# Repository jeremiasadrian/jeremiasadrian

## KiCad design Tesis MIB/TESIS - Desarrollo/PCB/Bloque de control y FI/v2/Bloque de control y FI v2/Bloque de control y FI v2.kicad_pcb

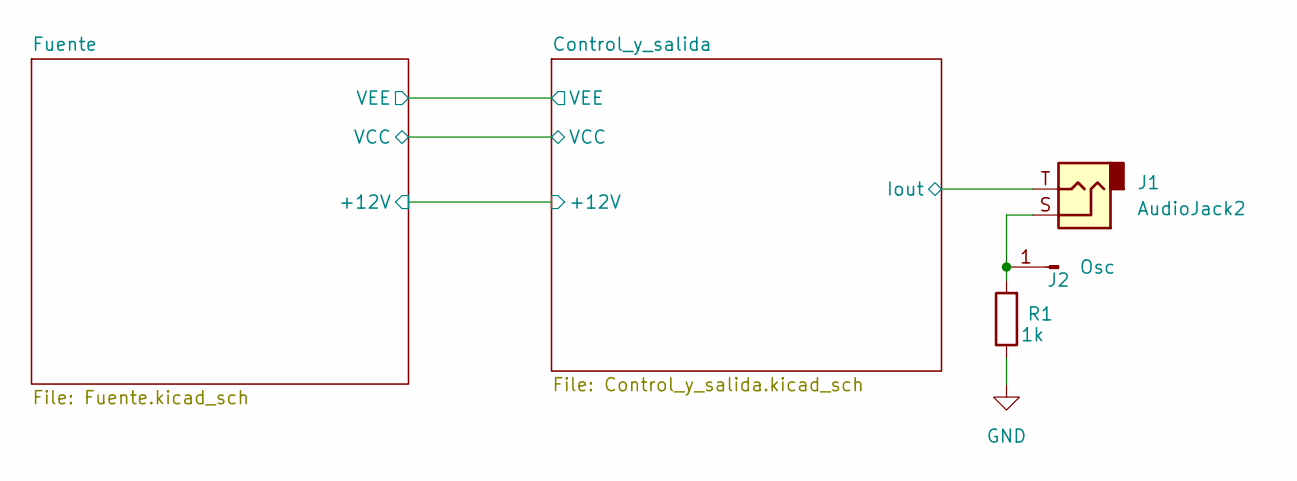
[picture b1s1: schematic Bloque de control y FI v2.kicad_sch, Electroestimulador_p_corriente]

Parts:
J1: AudioJack2; Jack_3.5mm_Ledino_KB3SPRS_Horizontal
J2: Osc; Pin_D0.9mm_L10.0mm_W2.4mm_FlatFork
R1: 1k; R_Axial_DIN0207_L6.3mm_D2.5mm_P10.16mm_Horizontal; Tolerancia 1%

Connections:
/Control_y_salida/Iout: J1.T; also elsewhere on the board
GND: R1.1; also elsewhere on the board
unnamed: J1.S, J2.1, R1.2

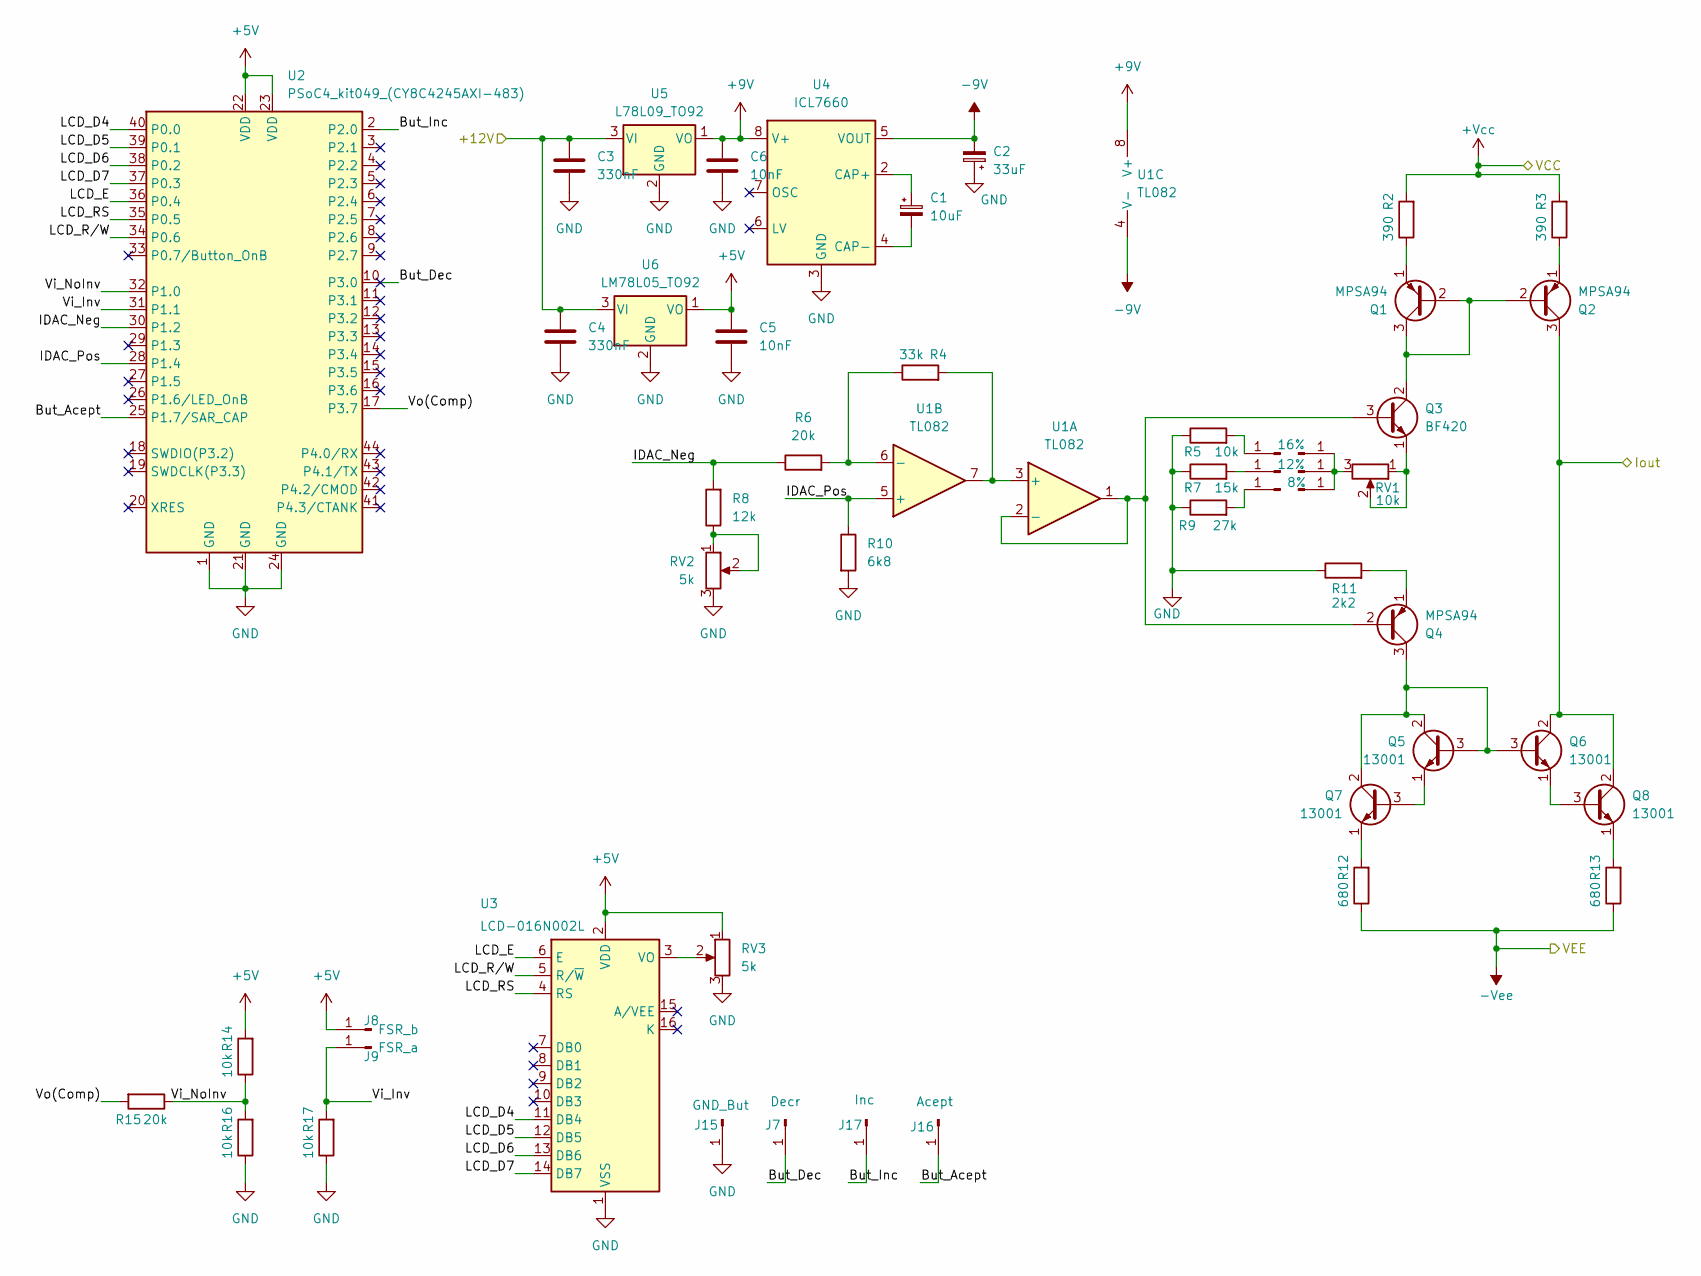
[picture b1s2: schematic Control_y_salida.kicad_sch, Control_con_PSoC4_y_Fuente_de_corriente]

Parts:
C1: 10uF; CP_Radial_D5.0mm_P2.50mm
C2: 33uF; CP_Radial_D5.0mm_P2.50mm
C3, C4: 330nF; C_Disc_D5.0mm_W2.5mm_P5.00mm
C5, C6: 10nF; C_Disc_D5.0mm_W2.5mm_P5.00mm
J5, J14: 16%; Pin_D0.9mm_L10.0mm_W2.4mm_FlatFork
J6, J12: 8%; Pin_D0.9mm_L10.0mm_W2.4mm_FlatFork
J7: Decr; Pin_D0.9mm_L10.0mm_W2.4mm_FlatFork
J8: FSR_b; Pin_D0.9mm_L10.0mm_W2.4mm_FlatFork
J9: FSR_a; Pin_D0.9mm_L10.0mm_W2.4mm_FlatFork
J11, J13: 12%; Pin_D0.9mm_L10.0mm_W2.4mm_FlatFork
J15: GND_But; Pin_D0.9mm_L10.0mm_W2.4mm_FlatFork
J16: Acept; Pin_D0.9mm_L10.0mm_W2.4mm_FlatFork
J17: Inc; Pin_D0.9mm_L10.0mm_W2.4mm_FlatFork
Q1, Q2, Q4: MPSA94; BF42X
Q3: BF420; BF42X
Q5, Q6, Q7, Q8: 13001; BF42X
R2, R3: 390; R_Axial_DIN0207_L6.3mm_D2.5mm_P10.16mm_Horizontal; Tolerancia 1%
R4: 33k; R_Axial_DIN0207_L6.3mm_D2.5mm_P10.16mm_Horizontal; Tolerancia 1%
R5, R14, R16, R17: 10k; R_Axial_DIN0207_L6.3mm_D2.5mm_P10.16mm_Horizontal; Tolerancia 1%
R6, R15: 20k; R_Axial_DIN0207_L6.3mm_D2.5mm_P10.16mm_Horizontal; Tolerancia 1%
R7: 15k; R_Axial_DIN0207_L6.3mm_D2.5mm_P10.16mm_Horizontal; Tolerancia 1%
R8: 12k; R_Axial_DIN0207_L6.3mm_D2.5mm_P10.16mm_Horizontal; Tolerancia 1%
R9: 27k; R_Axial_DIN0207_L6.3mm_D2.5mm_P10.16mm_Horizontal; Tolerancia 1%
R10: 6k8; R_Axial_DIN0207_L6.3mm_D2.5mm_P10.16mm_Horizontal; Tolerancia 1%
R11: 2k2; R_Axial_DIN0207_L6.3mm_D2.5mm_P10.16mm_Horizontal; Tolerancia 1%
R12, R13: 680; R_Axial_DIN0207_L6.3mm_D2.5mm_P10.16mm_Horizontal; Tolerancia 1%
RV1: 10k; Potentiometer_ACP_CA9-V10_Vertical
RV2, RV3: 5k; Potentiometer_Bourns_3296W_Vertical
U1: TL082; DIP-8_W7.62mm
U2: PSoC4_kit049_(CY8C4245AXI-483); PinSocket_2x22_P2.54mm_Vertical_3
U3: LCD-016N002L; LCD_pinsonly
U4: ICL7660; DIP-8_W7.62mm
U5: L78L09_TO92; TO-92_Inline_Wide
U6: LM78L05_TO92; TO-92_Inline_Wide

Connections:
+5V: C5.1, J8.1, R14.2, RV3.1, U2.22 (VDD), U2.23 (VDD), U3.2 (VDD), U6.1 (VO)
+9V: C6.1, U1.8 (V+), U4.8 (V+), U5.1 (VO)
-9V: C2.2, U1.4 (V-), U4.5 (VOUT)
/Control_y_salida/+12V: C3.1, C4.1, U5.3 (VI), U6.3 (VI); also elsewhere on the board
/Control_y_salida/But_Acept: J16.1, U2.25 (P1.7/SAR_CAP)
/Control_y_salida/But_Dec: J7.1, U2.10 (P3.0)
/Control_y_salida/But_Inc: J17.1, U2.2 (P2.0)
/Control_y_salida/IDAC_Neg: R6.1, R8.2, U2.30 (P1.2)
/Control_y_salida/IDAC_Pos: R10.1, U1.5 (+), U2.28 (P1.4)
/Control_y_salida/Iout: Q2.3 (C), Q6.2 (C), Q8.2 (C); also elsewhere on the board
/Control_y_salida/LCD_D4: U2.40 (P0.0), U3.11 (DB4)
/Control_y_salida/LCD_D5: U2.39 (P0.1), U3.12 (DB5)
/Control_y_salida/LCD_D6: U2.38 (P0.2), U3.13 (DB6)
/Control_y_salida/LCD_D7: U2.37 (P0.3), U3.14 (DB7)
/Control_y_salida/LCD_E: U2.36 (P0.4), U3.6 (E)
/Control_y_salida/LCD_RS: U2.35 (P0.5), U3.4 (RS)
/Control_y_salida/LCD_R/W: U2.34 (P0.6), U3.5 (R/~W)
/Control_y_salida/Vi_Inv: J9.1, R17.2, U2.31 (P1.1)
/Control_y_salida/Vi_NoInv: R14.1, R15.1, R16.2, U2.32 (P1.0)
/Control_y_salida/Vo(Comp): R15.2, U2.17 (P3.7)
GND: C2.1, C3.2, C4.2, C5.2, C6.2, J15.1, R5.1, R7.1, R9.1, R10.2, R11.1, R16.1, R17.1, RV2.3, RV3.3, U2.1 (GND), U2.21 (GND), U2.24 (GND), U3.1 (VSS), U4.3 (GND), U5.2 (GND), U6.2 (GND); also elsewhere on the board
unnamed: J5.1, R5.2
unnamed: J11.1, R7.2
unnamed: J12.1, R9.2
unnamed: J6.1, J13.1, J14.1, RV1.3
unnamed: Q1.2 (B), Q1.3 (C), Q2.2 (B), Q3.2 (C)
unnamed: Q1.1 (E), R2.1
unnamed: Q2.1 (E), R3.1
unnamed: Q3.3 (B), Q4.2 (B), U1.1, U1.2 (-)
unnamed: Q3.1 (E), RV1.1, RV1.2
unnamed: Q4.3 (C), Q5.2 (C), Q5.3 (B), Q6.3 (B), Q7.2 (C)
unnamed: Q4.1 (E), R11.2
unnamed: Q5.1 (E), Q7.3 (B)
unnamed: Q6.1 (E), Q8.3 (B)
unnamed: Q7.1 (E), R12.2
unnamed: Q8.1 (E), R13.2
unnamed: R8.1, RV2.1, RV2.2
unnamed: R4.2, U1.3 (+), U1.7
unnamed: R4.1, R6.2, U1.6 (-)
unnamed: RV3.2, U3.3 (VO)
unnamed: C1.1, U4.2 (CAP+)
unnamed: C1.2, U4.4 (CAP-)
VCC: R2.2, R3.2; also elsewhere on the board
VEE: R12.1, R13.1; also elsewhere on the board

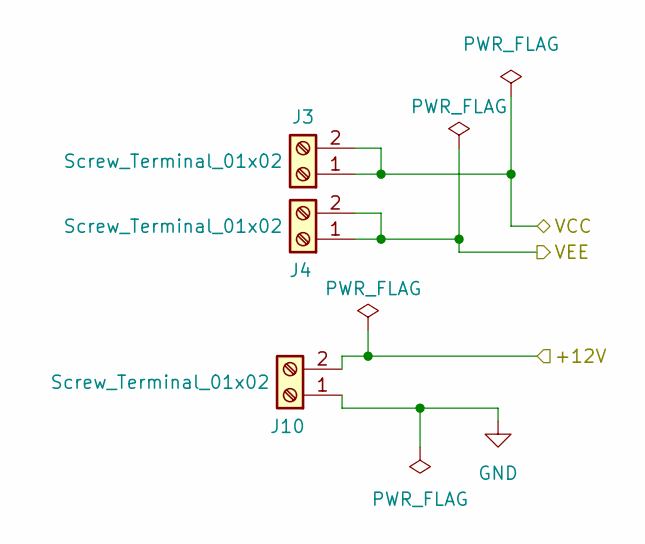
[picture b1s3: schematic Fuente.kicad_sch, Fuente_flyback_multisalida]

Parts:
J3, J4, J10: Screw_Terminal_01x02; TerminalBlock_bornier-2_P5.08mm

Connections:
/Control_y_salida/+12V: J10.2; also elsewhere on the board
GND: J10.1; also elsewhere on the board
VCC: J3.1, J3.2; also elsewhere on the board
VEE: J4.1, J4.2; also elsewhere on the board

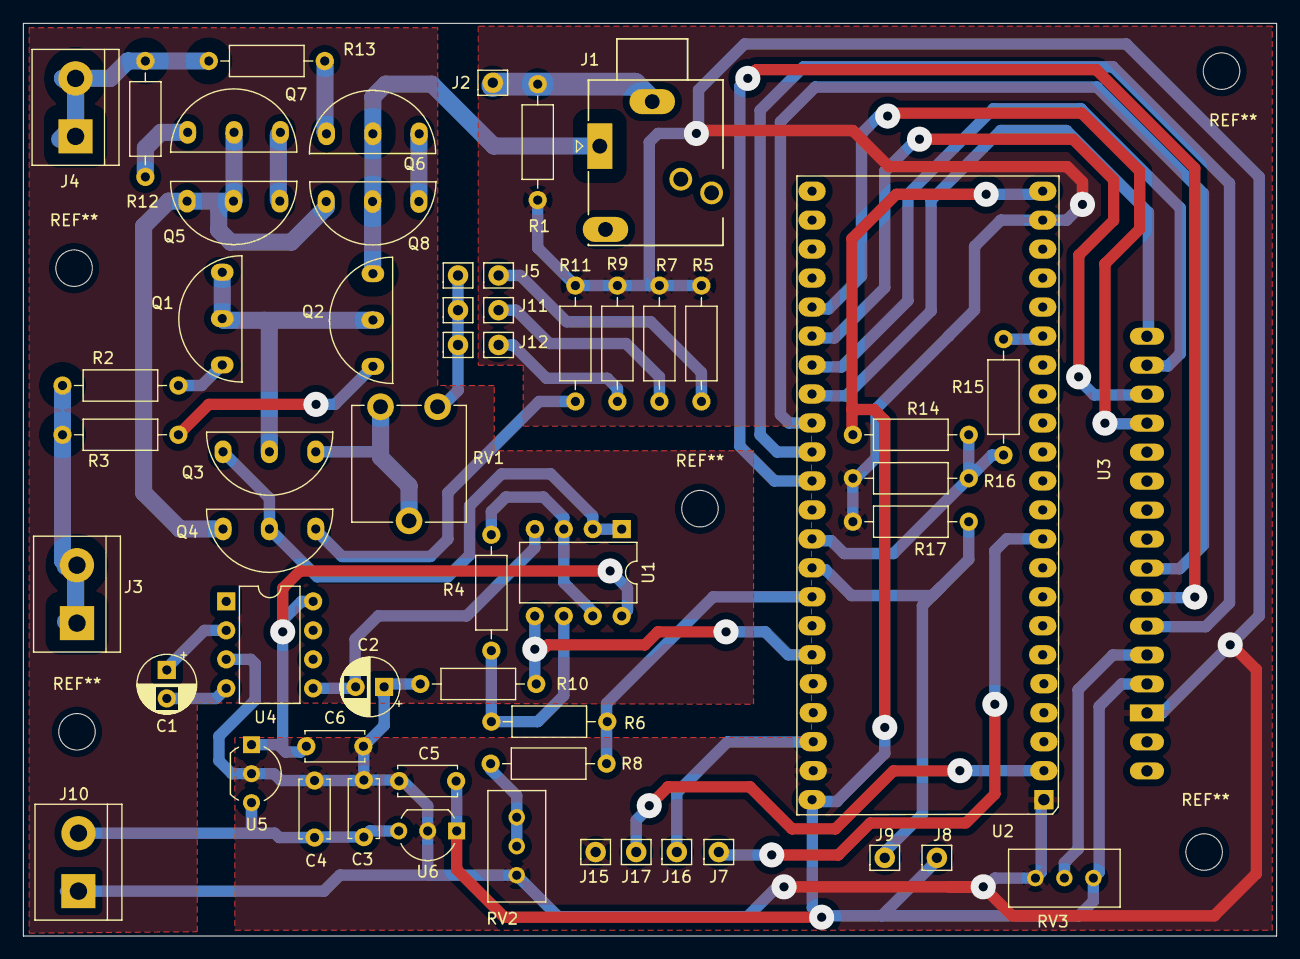
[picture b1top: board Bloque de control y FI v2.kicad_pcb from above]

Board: 2 copper layers, 109.9 x 80.0 mm, 57 parts (0 on the bottom side), 45 nets.

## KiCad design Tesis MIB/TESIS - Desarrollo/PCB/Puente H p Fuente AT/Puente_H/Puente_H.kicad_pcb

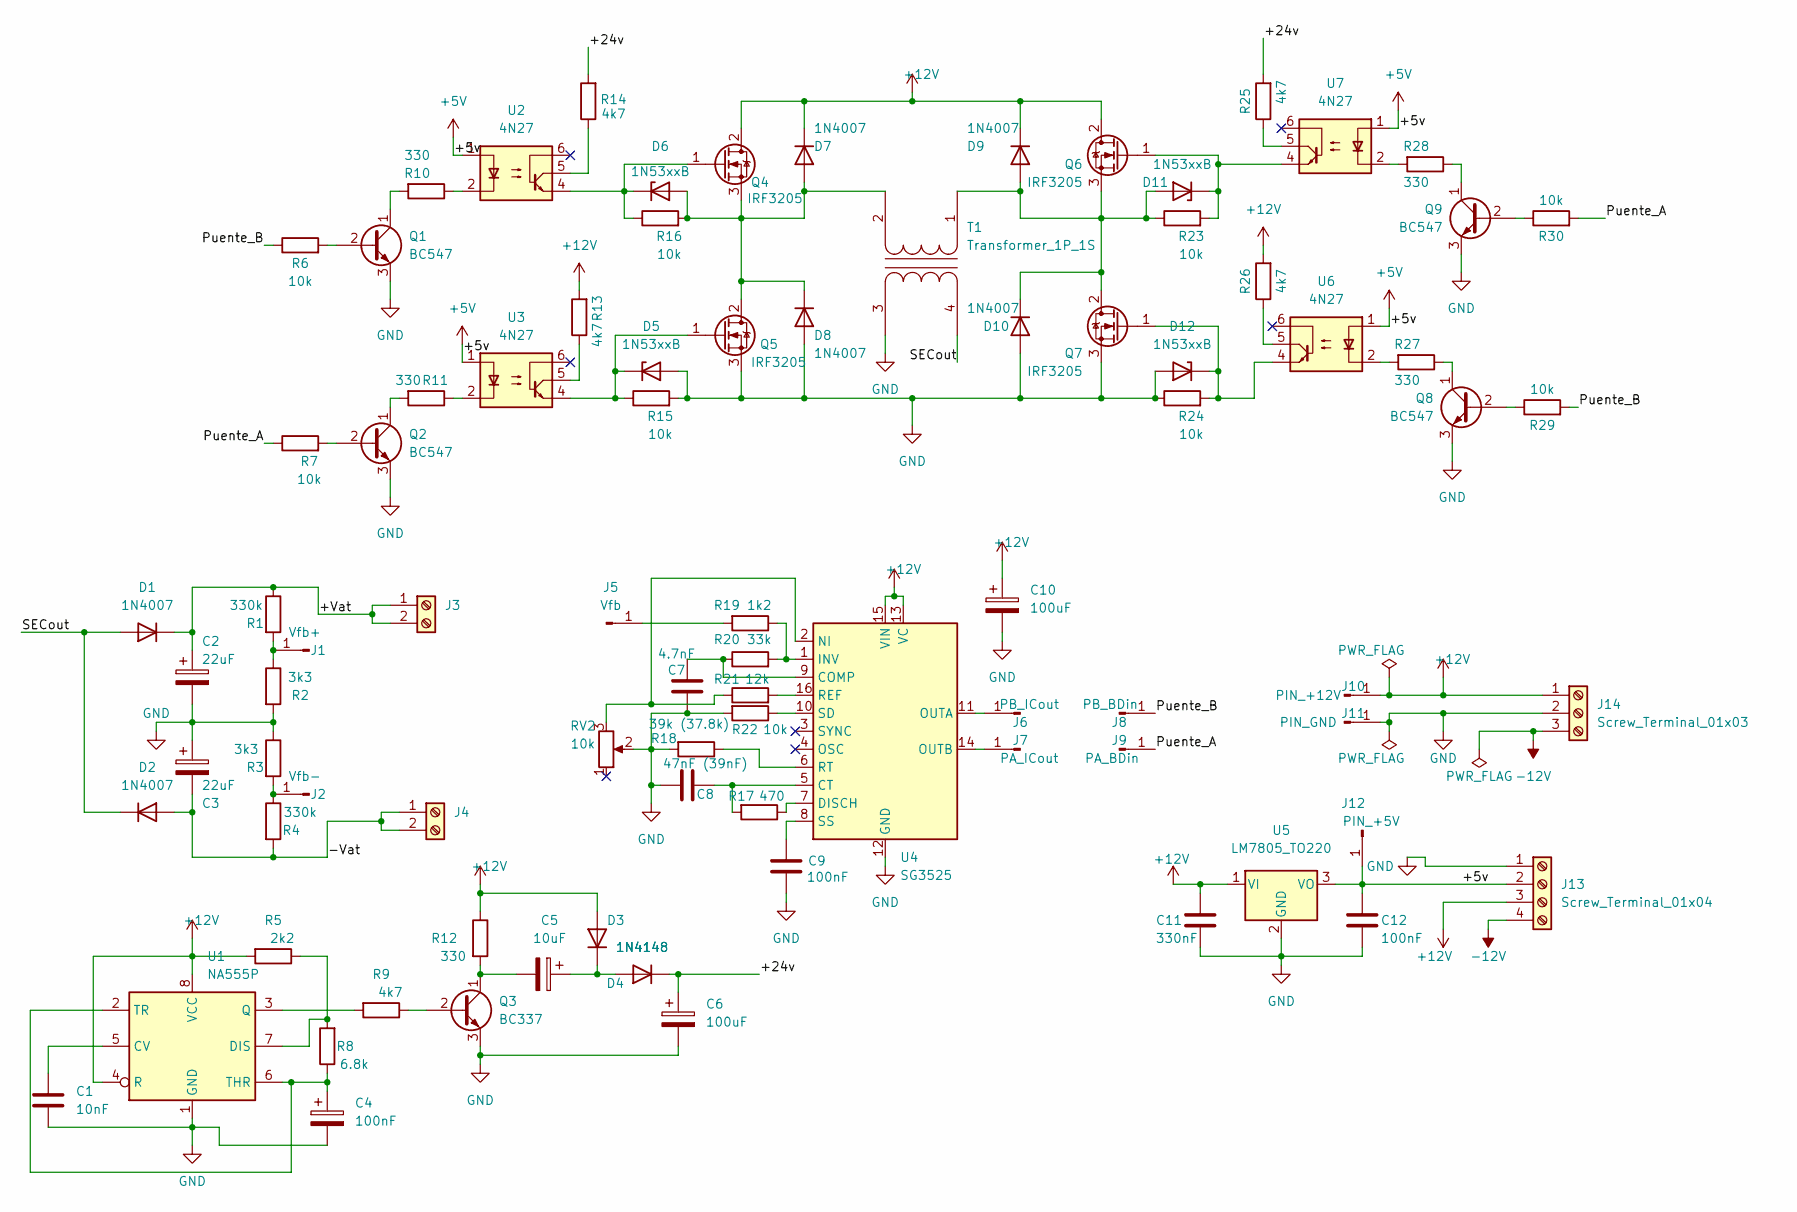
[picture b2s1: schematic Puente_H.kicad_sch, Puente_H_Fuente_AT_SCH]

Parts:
C1: 10nF; C_Disc_D5.0mm_W2.5mm_P2.50mm
C2, C3: 22uF; CP_Radial_D16.0mm_P7.50mm
C4, C9, C12: 100nF; C_Disc_D5.0mm_W2.5mm_P2.50mm
C5: 10uF; CP_Radial_D6.3mm_P2.50mm
C6, C10: 100uF; CP_Radial_D6.3mm_P2.50mm
C7: 4.7nF; C_Disc_D5.0mm_W2.5mm_P2.50mm
C8: 47nF (39nF); C_Disc_D5.0mm_W2.5mm_P2.50mm
C11: 330nF; C_Disc_D5.0mm_W2.5mm_P2.50mm
D1, D2, D7, D8, D9, D10: 1N4007; D_DO-41_SOD81_P10.16mm_Horizontal
D3, D4: 1N4148; D_DO-35_SOD27_P7.62mm_Horizontal
D5, D6, D11, D12: 1N53xxB; D_DO-35_SOD27_P7.62mm_Horizontal
J1: Vfb+; Pin_D0.7mm_L6.5mm_W1.8mm_FlatFork
J2: Vfb-; Pin_D0.7mm_L6.5mm_W1.8mm_FlatFork
J3, J4: Screw_Terminal_01x02; TerminalBlock_bornier-2_P5.08mm
J5: Vfb; Pin_D0.7mm_L6.5mm_W1.8mm_FlatFork
J6: PB_ICout; Pin_D0.7mm_L6.5mm_W1.8mm_FlatFork
J7: PA_ICout; Pin_D0.7mm_L6.5mm_W1.8mm_FlatFork
J8: PB_BDin; Pin_D0.7mm_L6.5mm_W1.8mm_FlatFork
J9: PA_BDin; Pin_D0.7mm_L6.5mm_W1.8mm_FlatFork
J10: PIN_+12V; Pin_D0.7mm_L6.5mm_W1.8mm_FlatFork
J11: PIN_GND; Pin_D0.7mm_L6.5mm_W1.8mm_FlatFork
J12: PIN_+5V; Pin_D0.7mm_L6.5mm_W1.8mm_FlatFork
J13: Screw_Terminal_01x04; TerminalBlock_bornier-4_P5.08mm
J14: Screw_Terminal_01x03; TerminalBlock_bornier-3_P5.08mm
Q1, Q2, Q8, Q9: BC547; TO-92_Inline_Wide
Q3: BC337; TO-92_Inline_Wide
Q4, Q5, Q6, Q7: IRF3205; TO-220-3_Vertical
R1, R4: 330k; R_Axial_DIN0207_L6.3mm_D2.5mm_P7.62mm_Horizontal
R2, R3: 3k3; R_Axial_DIN0207_L6.3mm_D2.5mm_P7.62mm_Horizontal
R5: 2k2; R_Axial_DIN0207_L6.3mm_D2.5mm_P7.62mm_Horizontal
R6, R7, R15, R16, R22, R23, R24, R29, R30: 10k; R_Axial_DIN0207_L6.3mm_D2.5mm_P7.62mm_Horizontal
R8: 6.8k; R_Axial_DIN0207_L6.3mm_D2.5mm_P7.62mm_Horizontal
R9, R13, R14, R25, R26: 4k7; R_Axial_DIN0207_L6.3mm_D2.5mm_P7.62mm_Horizontal
R10, R11, R12, R27, R28: 330; R_Axial_DIN0207_L6.3mm_D2.5mm_P7.62mm_Horizontal
R17: 470; R_Axial_DIN0207_L6.3mm_D2.5mm_P7.62mm_Horizontal
R18: 39k (37.8k); R_Axial_DIN0207_L6.3mm_D2.5mm_P7.62mm_Horizontal
R19: 1k2; R_Axial_DIN0207_L6.3mm_D2.5mm_P7.62mm_Horizontal
R20: 33k; R_Axial_DIN0207_L6.3mm_D2.5mm_P7.62mm_Horizontal
R21: 12k; R_Axial_DIN0207_L6.3mm_D2.5mm_P7.62mm_Horizontal
RV2: 10k; Potentiometer_Bourns_3296W_Vertical
T1: Transformer_1P_1S; Transformer_1S_2P
U1: NA555P; DIP-8_W7.62mm
U2, U3, U6, U7: 4N27; DIP-6_W7.62mm
U4: SG3525; DIP-16_W7.62mm_LongPads
U5: LM7805_TO220; TO-220-3_Vertical

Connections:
+5V: C12.1, J12.1, J13.2, U2.1, U3.1, U5.3 (VO), U6.1, U7.1
+12V: C10.1, C11.1, D3.2 (A), D7.1 (K), D9.1 (K), J10.1, J13.3, J14.1, Q4.2 (D), Q6.2 (D), R5.2, R12.1, R13.2, R26.2, U1.4 (R), U1.8 (VCC), U4.13 (VC), U4.15 (VIN), U5.1 (VI)
-12V: J13.4, J14.3
/+24v: C6.1, D4.1 (K), R14.2, R25.2
/+Vat: C2.1, D1.1 (K), J3.1, J3.2, R1.1
/-Vat: C3.2, D2.2 (A), J4.1, J4.2, R4.2
/Puente_A: J9.1, R7.1, R30.2
/Puente_B: J8.1, R6.1, R29.2
/SECout: D1.2 (A), D2.1 (K), T1.4 (SB)
GND: C1.2, C2.2, C3.1, C4.2, C6.2, C7.2, C8.1, C9.1, C10.2, C11.2, C12.2, D5.2 (A), D8.2 (A), D10.2 (A), D12.2 (A), J11.1, J13.1, J14.2, Q1.3 (E), Q2.3 (E), Q3.3 (E), Q5.3 (S), Q7.3 (S), Q8.3 (E), Q9.3 (E), R2.2, R3.1, R15.2, R18.2, R22.2, R24.1, RV2.2, T1.3 (SA), U1.1 (GND), U4.12 (GND), U5.2 (GND)
unnamed: C5.1, D3.1 (K), D4.2 (A)
unnamed: D5.1 (K), Q5.1 (G), R15.1, U3.4
unnamed: D6.2 (A), D7.2 (A), D8.1 (K), Q4.3 (S), Q5.2 (D), R16.2, T1.2 (AB)
unnamed: D6.1 (K), Q4.1 (G), R16.1, U2.4
unnamed: D9.2 (A), D10.1 (K), D11.2 (A), Q6.3 (S), Q7.2 (D), R23.1, T1.1 (AA)
unnamed: D11.1 (K), Q6.1 (G), R23.2, U7.4
unnamed: D12.1 (K), Q7.1 (G), R24.2, U6.4
unnamed: J1.1, R1.2, R2.1
unnamed: J2.1, R3.2, R4.1
unnamed: J5.1, R19.2
unnamed: J6.1, U4.11 (OUTA)
unnamed: J7.1, U4.14 (OUTB)
unnamed: Q1.2 (B), R6.2
unnamed: Q1.1 (C), R10.2
unnamed: Q2.2 (B), R7.2
unnamed: Q2.1 (C), R11.2
unnamed: Q3.2 (B), R9.1
unnamed: C5.2, Q3.1 (C), R12.2
unnamed: Q8.2 (B), R29.1
unnamed: Q8.1 (C), R27.1
unnamed: Q9.2 (B), R30.1
unnamed: Q9.1 (C), R28.1
unnamed: R10.1, U2.2
unnamed: R11.1, U3.2
unnamed: R13.1, U3.5
unnamed: R14.1, U2.5
unnamed: R25.1, U7.5
unnamed: R26.1, U6.5
unnamed: R27.2, U6.2
unnamed: R28.2, U7.2
unnamed: C1.1, U1.5 (CV)
unnamed: R5.1, R8.2, U1.7 (DIS)
unnamed: R9.2, U1.3 (Q)
unnamed: C4.1, R8.1, U1.2 (TR), U1.6 (THR)
unnamed: C7.1, R20.1, U4.9 (COMP)
unnamed: C8.2, R17.2, U4.5 (CT)
unnamed: R17.1, U4.7 (DISCH)
unnamed: R19.1, R20.2, U4.1 (INV)
unnamed: R21.1, RV2.3, U4.2 (NI)
unnamed: R21.2, U4.16 (REF)
unnamed: R18.1, U4.6 (RT)
unnamed: R22.1, U4.10 (SD)
unnamed: C9.2, U4.8 (SS)

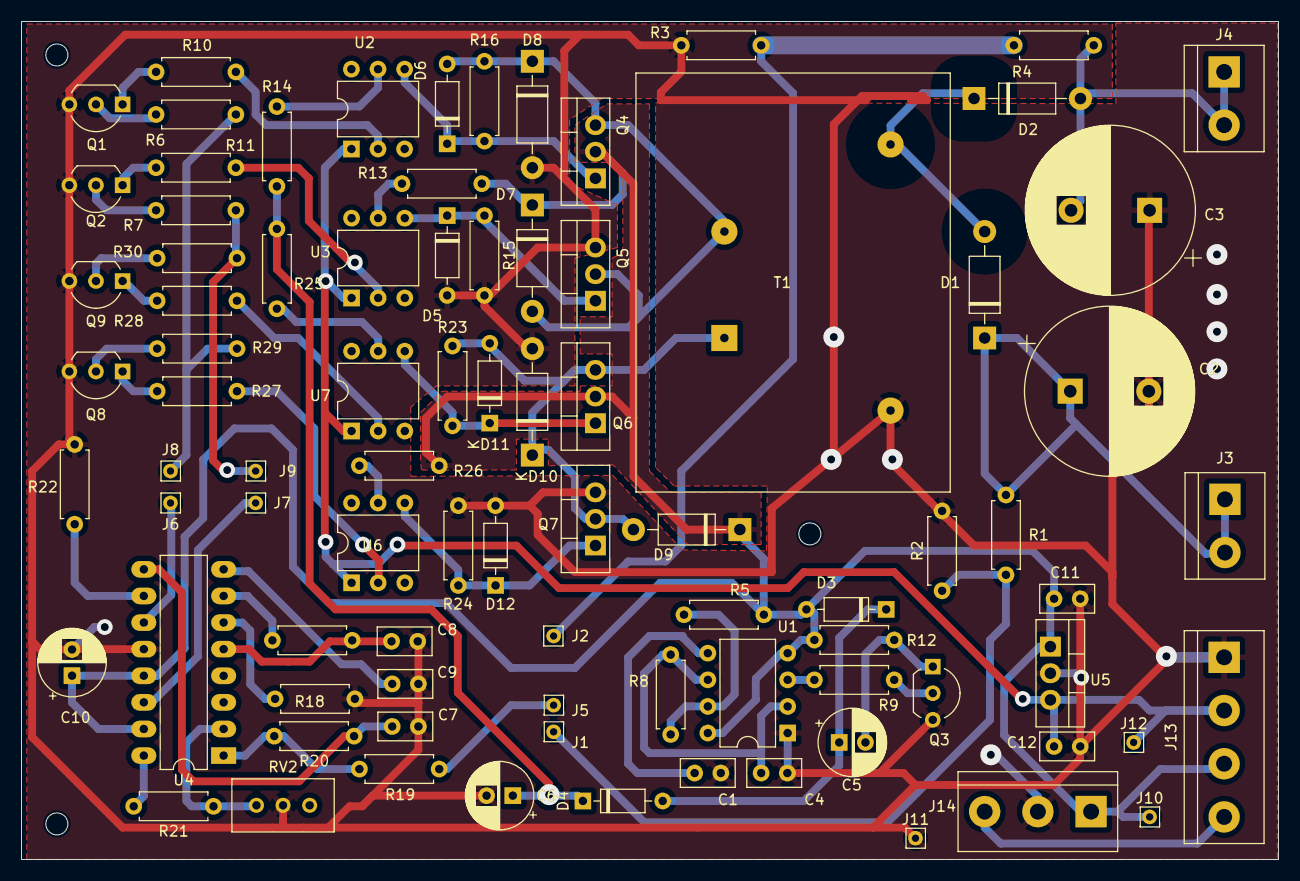
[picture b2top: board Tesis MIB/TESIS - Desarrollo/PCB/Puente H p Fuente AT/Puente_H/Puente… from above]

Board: 2 copper layers, 120.0 x 80.0 mm, 89 parts (0 on the bottom side), 53 nets.

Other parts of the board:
REF01, REF02, REF03: MountingHole_2.1mm

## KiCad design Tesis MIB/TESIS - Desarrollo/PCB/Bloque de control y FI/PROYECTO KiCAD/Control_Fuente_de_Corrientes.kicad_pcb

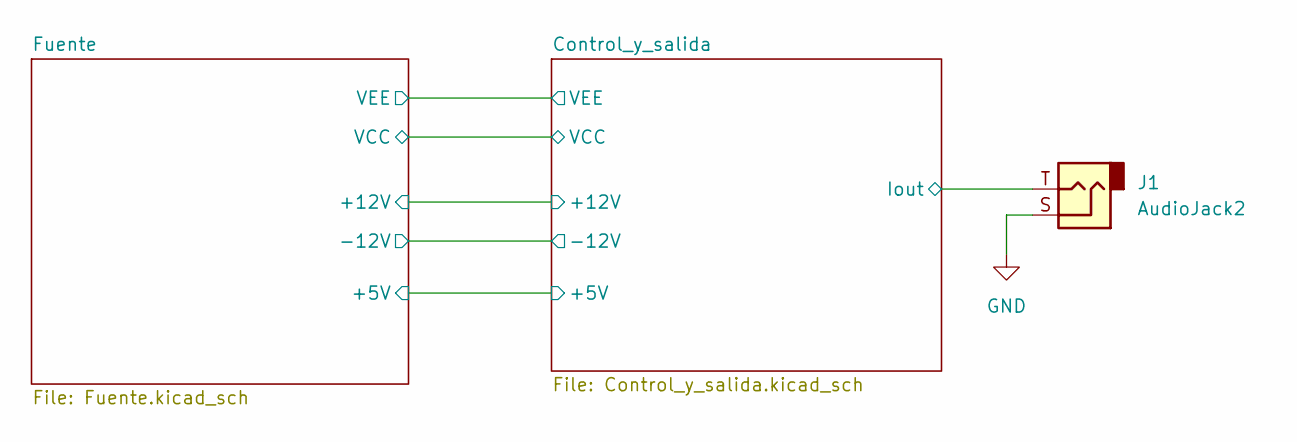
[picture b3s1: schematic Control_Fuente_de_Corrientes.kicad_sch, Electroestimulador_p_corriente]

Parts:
J1: AudioJack2; Jack_3.5mm_Ledino_KB3SPRS_Horizontal

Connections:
/Control_y_salida/Iout: J1.T; also elsewhere on the board
GND: J1.S; also elsewhere on the board

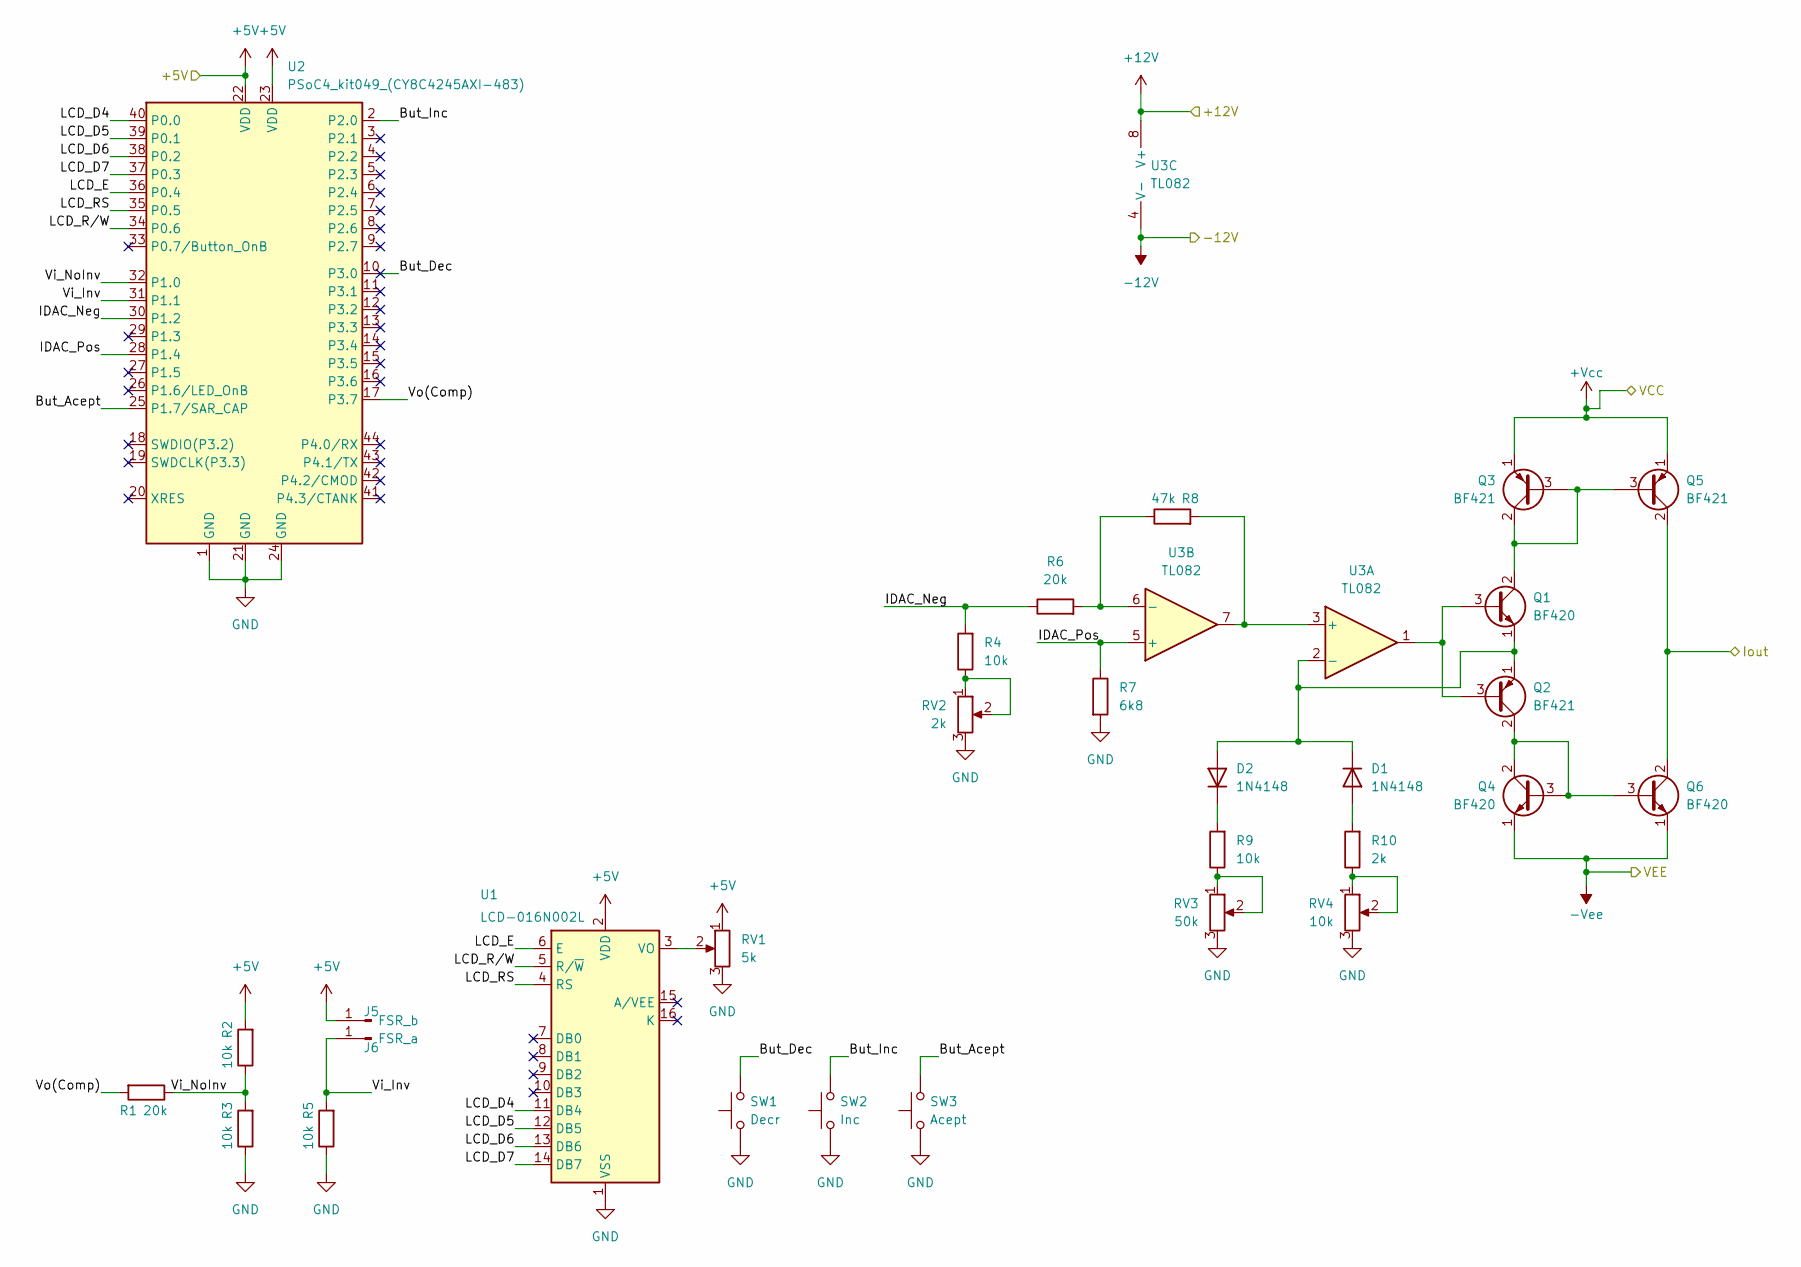
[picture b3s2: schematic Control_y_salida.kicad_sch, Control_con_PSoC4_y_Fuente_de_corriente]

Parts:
D1, D2: 1N4148; D_DO-41_SOD81_P7.62mm_Horizontal
J5: FSR_b; Pin_D0.9mm_L10.0mm_W2.4mm_FlatFork
J6: FSR_a; Pin_D0.9mm_L10.0mm_W2.4mm_FlatFork
Q1, Q4, Q6: BF420; BF42X
Q2, Q3, Q5: BF421; BF42X
R1, R6: 20k; R_Axial_DIN0207_L6.3mm_D2.5mm_P10.16mm_Horizontal; Tolerancia 1%
R2, R3, R4, R5, R9: 10k; R_Axial_DIN0207_L6.3mm_D2.5mm_P10.16mm_Horizontal; Tolerancia 1%
R7: 6k8; R_Axial_DIN0207_L6.3mm_D2.5mm_P10.16mm_Horizontal; Tolerancia 1%
R8: 47k; R_Axial_DIN0207_L6.3mm_D2.5mm_P10.16mm_Horizontal; Tolerancia 1%
R10: 2k; R_Axial_DIN0207_L6.3mm_D2.5mm_P10.16mm_Horizontal; Tolerancia 1%
RV1: 5k; Potentiometer_Bourns_3296W_Vertical
RV2: 2k; Potentiometer_Bourns_3296W_Vertical
RV3: 50k; Potentiometer_Bourns_3296W_Vertical
RV4: 10k; Potentiometer_Bourns_3296W_Vertical
SW1: Decr; SW_PUSH_6mm_H7.3mm
SW2: Inc; SW_PUSH_6mm_H7.3mm
SW3: Acept; SW_PUSH_6mm_H7.3mm
U1: LCD-016N002L; LCD_pinsonly
U2: PSoC4_kit049_(CY8C4245AXI-483); PinSocket_2x22_P2.54mm_Vertical_3
U3: TL082; DIP-8_W10.16mm_LongPads

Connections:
+5V: J5.1, R2.2, RV1.1, U1.2 (VDD), U2.22 (VDD), U2.23 (VDD); also elsewhere on the board
+12V: U3.8 (V+); also elsewhere on the board
-12V: U3.4 (V-); also elsewhere on the board
/Control_y_salida/But_Acept: SW3.2, U2.25 (P1.7/SAR_CAP)
/Control_y_salida/But_Dec: SW1.2, U2.10 (P3.0)
/Control_y_salida/But_Inc: SW2.2, U2.2 (P2.0)
/Control_y_salida/IDAC_Neg: R4.2, R6.1, U2.30 (P1.2)
/Control_y_salida/IDAC_Pos: R7.1, U2.28 (P1.4), U3.5 (+)
/Control_y_salida/Iout: Q5.2 (C), Q6.2 (C); also elsewhere on the board
/Control_y_salida/LCD_D4: U1.11 (DB4), U2.40 (P0.0)
/Control_y_salida/LCD_D5: U1.12 (DB5), U2.39 (P0.1)
/Control_y_salida/LCD_D6: U1.13 (DB6), U2.38 (P0.2)
/Control_y_salida/LCD_D7: U1.14 (DB7), U2.37 (P0.3)
/Control_y_salida/LCD_E: U1.6 (E), U2.36 (P0.4)
/Control_y_salida/LCD_RS: U1.4 (RS), U2.35 (P0.5)
/Control_y_salida/LCD_R/W: U1.5 (R/~W), U2.34 (P0.6)
/Control_y_salida/Vi_Inv: J6.1, R5.2, U2.31 (P1.1)
/Control_y_salida/Vi_NoInv: R1.1, R2.1, R3.2, U2.32 (P1.0)
GND: R3.1, R5.1, R7.2, RV1.3, RV2.3, RV3.3, RV4.3, SW1.1, SW2.1, SW3.1, U1.1 (VSS), U2.1 (GND), U2.21 (GND), U2.24 (GND); also elsewhere on the board
unnamed: D1.2 (A), R10.2
unnamed: D1.1 (K), D2.2 (A), Q1.1 (E), Q2.1 (E), U3.2 (-)
unnamed: D2.1 (K), R9.2
unnamed: Q1.3 (B), Q2.3 (B), U3.1
unnamed: Q1.2 (C), Q3.2 (C), Q3.3 (B), Q5.3 (B)
unnamed: Q2.2 (C), Q4.2 (C), Q4.3 (B), Q6.3 (B)
unnamed: R4.1, RV2.1, RV2.2
unnamed: R9.1, RV3.1, RV3.2
unnamed: R10.1, RV4.1, RV4.2
unnamed: RV1.2, U1.3 (VO)
unnamed: R1.2, U2.17 (P3.7)
unnamed: R8.2, U3.3 (+), U3.7
unnamed: R6.2, R8.1, U3.6 (-)
VCC: Q3.1 (E), Q5.1 (E); also elsewhere on the board
VEE: Q4.1 (E), Q6.1 (E); also elsewhere on the board

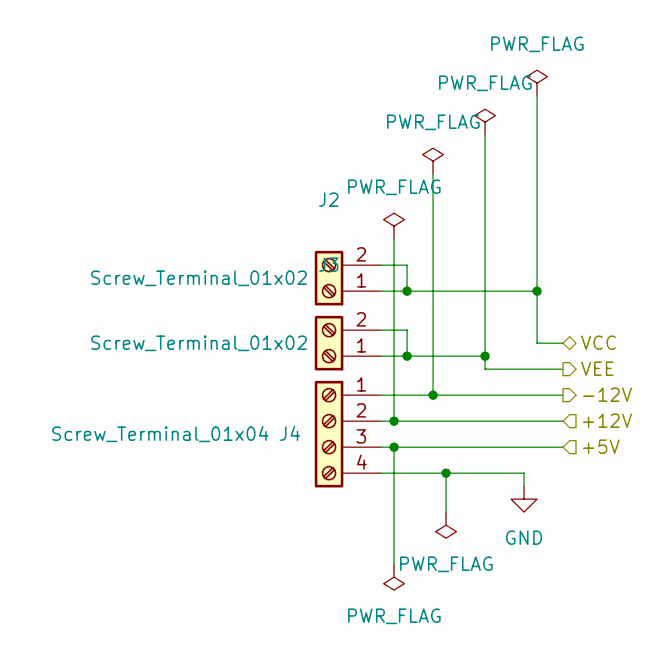
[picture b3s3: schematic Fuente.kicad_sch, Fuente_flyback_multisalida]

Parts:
J2, J3: Screw_Terminal_01x02; TerminalBlock_bornier-2_P5.08mm
J4: Screw_Terminal_01x04; TerminalBlock_bornier-4_P5.08mm

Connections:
+5V: J4.3; also elsewhere on the board
+12V: J4.2; also elsewhere on the board
-12V: J4.1; also elsewhere on the board
GND: J4.4; also elsewhere on the board
VCC: J2.1, J2.2; also elsewhere on the board
VEE: J3.1, J3.2; also elsewhere on the board

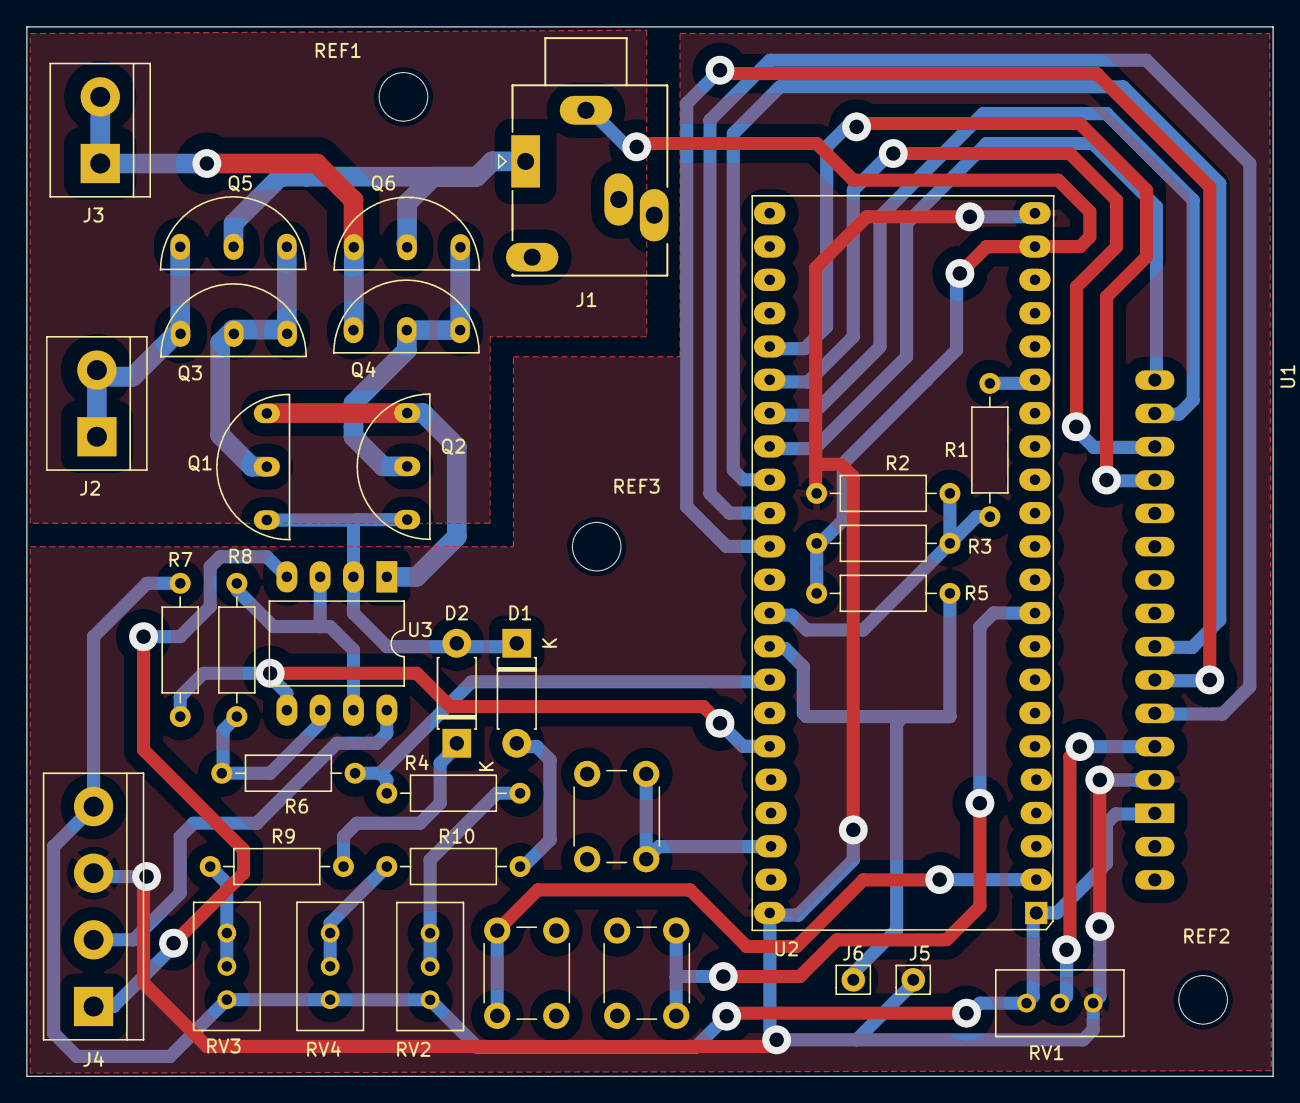
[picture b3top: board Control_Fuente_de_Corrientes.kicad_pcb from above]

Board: 2 copper layers, 95.0 x 80.0 mm, 37 parts (0 on the bottom side), 34 nets.

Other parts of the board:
REF1, REF2, REF3: MountingHole_3.7mm
